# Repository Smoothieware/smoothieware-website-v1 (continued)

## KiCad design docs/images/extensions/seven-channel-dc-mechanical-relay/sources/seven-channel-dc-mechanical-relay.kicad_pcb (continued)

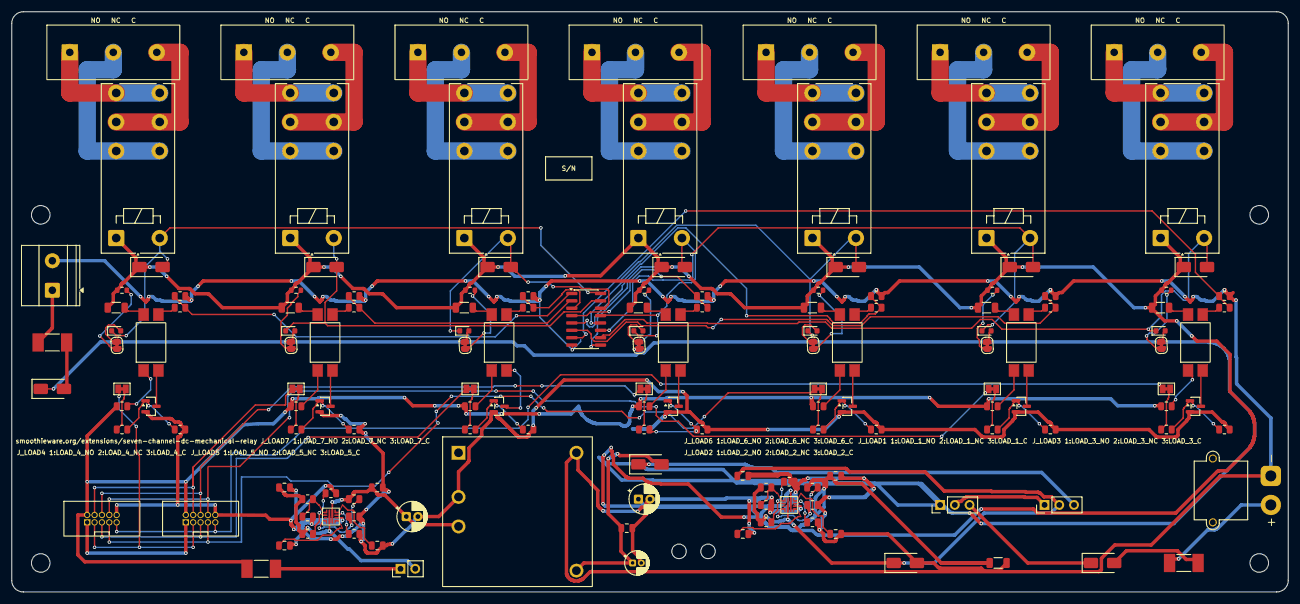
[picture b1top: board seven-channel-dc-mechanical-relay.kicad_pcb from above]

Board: 2 copper layers, 220.0 x 100.0 mm, 157 parts (1 on the bottom side), 128 nets.

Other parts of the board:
CT1, CT2: CABLE TIE; CableTie_NPTH_2_5mm
H1, H2, H3, H4: MountingHole_3.2mm_M3

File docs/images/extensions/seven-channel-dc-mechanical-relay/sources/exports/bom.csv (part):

Reference,Value,Footprint,DNP,Excluded_from_BOM,Manufacturer_part_number,Procurement_status,Assembly_role
CT1,CABLE TIE,Fancification_Mechanical:CableTie_NPTH_2_5mm,False,True,,Retained baseline item; exact procurement mapping/availability requires review,Mechanical/no purchase line
CT2,CABLE TIE,Fancification_Mechanical:CableTie_NPTH_2_5mm,False,True,,Retained baseline item; exact procurement mapping/availability requires review,Mechanical/no purchase line
C_ARRAY1,885012207098,Capacitor_SMD:C_0805_2012Metric,False,False,885012207098,Exact ordering choice; supplier stock/format/MOQ not qualified,SMT; assembler eligibility/orientation requires approval
C_COIL_BULK1,47uF 25V,Capacitor_THT:CP_Radial_D5.0mm_P2.00mm,False,False,EEUFR1E470,Exact ordering choice; supplier stock/format/MOQ not qualified,Through-hole hand-fit; exclude from SMT placement import
C_COIL_DVDT1,10nF 50V,Capacitor_SMD:C_0805_2012Metric,False,False,,Retained baseline item; exact procurement mapping/availability requires review,SMT; assembler eligibility/orientation requires approval
C_COIL_IN1,100nF 35V,Capacitor_SMD:C_0805_2012Metric,False,False,,Retained baseline item; exact procurement mapping/availability requires review,SMT; assembler eligibility/orientation requires approval
C_COIL_ITIMER1,2.2nF 16V,Capacitor_SMD:C_0805_2012Metric,False,False,,Retained baseline item; exact procurement mapping/availability requires review,SMT; assembler eligibility/orientation requires approval
C_COIL_OUT1,100nF 35V,Capacitor_SMD:C_0805_2012Metric,False,False,,Retained baseline item; exact procurement mapping/availability requires review,SMT; assembler eligibility/orientation requires approval
C_HOST_DVDT1,10nF 50V,Capacitor_SMD:C_0805_2012Metric,False,False,,Retained baseline item; exact procurement mapping/availability requires review,SMT; assembler eligibility/orientation requires approval
C_HOST_IN1,100nF 25V,Capacitor_SMD:C_0805_2012Metric,False,False,,Retained baseline item; exact procurement mapping/availability requires review,SMT; assembler eligibility/orientation requires approval
C_HOST_ITIMER1,2.2nF 16V,Capacitor_SMD:C_0805_2012Metric,False,False,,Retained baseline item; exact procurement mapping/availability requires review,SMT; assembler eligibility/orientation requires approval
C_HOST_OUT1,100nF 25V,Capacitor_SMD:C_0805_2012Metric,False,False,,Retained baseline item; exact procurement mapping/availability requires review,SMT; assembler eligibility/orientation requires approval
C_ISO_BYP1,100nF 25V,Capacitor_SMD:C_0805_2012Metric,False,False,,Retained baseline item; exact procurement mapping/availability requires review,SMT; assembler eligibility/orientation requires approval
C_ISO_IN1,100uF 16V,Capacitor_THT:CP_Radial_D5.0mm_P2.00mm,False,False,,Retained baseline item; exact procurement mapping/availability requires review,Through-hole hand-fit; exclude from SMT placement import
C_ISO_PRE1,10uF 25V,Capacitor_THT:CP_Radial_D4.0mm_P1.50mm,False,False,,Retained baseline item; exact procurement mapping/availability requires review,Through-hole hand-fit; exclude from SMT placement import
D_FLY1,SS16-E3/61T,Diode_SMD:D_SMA,False,False,,Retained baseline item; exact procurement mapping/availability requires review,SMT; assembler eligibility/orientation requires approval
D_FLY2,SS16-E3/61T,Diode_SMD:D_SMA,False,False,,Retained baseline item; exact procurement mapping/availability requires review,SMT; assembler eligibility/orientation requires approval
D_FLY3,SS16-E3/61T,Diode_SMD:D_SMA,False,False,,Retained baseline item; exact procurement mapping/availability requires review,SMT; assembler eligibility/orientation requires approval
D_FLY4,SS16-E3/61T,Diode_SMD:D_SMA,False,False,,Retained baseline item; exact procurement mapping/availability requires review,SMT; assembler eligibility/orientation requires approval
D_FLY5,SS16-E3/61T,Diode_SMD:D_SMA,False,False,,Retained baseline item; exact procurement mapping/availability requires review,SMT; assembler eligibility/orientation requires approval
D_FLY6,SS16-E3/61T,Diode_SMD:D_SMA,False,False,,Retained baseline item; exact procurement mapping/availability requires review,SMT; assembler eligibility/orientation requires approval
D_FLY7,SS16-E3/61T,Diode_SMD:D_SMA,False,False,,Retained baseline item; exact procurement mapping/availability requires review,SMT; assembler eligibility/orientation requires approval
D_IND1,GREEN,LED_SMD:LED_0603_1608Metric,False,False,,Retained baseline item; exact procurement mapping/availability requires review,SMT; assembler eligibility/orientation requires approval
D_IND2,GREEN,LED_SMD:LED_0603_1608Metric,False,False,,Retained baseline item; exact procurement mapping/availability requires review,SMT; assembler eligibility/orientation requires approval
D_IND3,GREEN,LED_SMD:LED_0603_1608Metric,False,False,,Retained baseline item; exact procurement mapping/availability requires review,SMT; assembler eligibility/orientation requires approval
D_IND4,GREEN,LED_SMD:LED_0603_1608Metric,False,False,,Retained baseline item; exact procurement mapping/availability requires review,SMT; assembler eligibility/orientation requires approval
D_IND5,GREEN,LED_SMD:LED_0603_1608Metric,False,False,,Retained baseline item; exact procurement mapping/availability requires review,SMT; assembler eligibility/orientation requires approval
D_IND6,GREEN,LED_SMD:LED_0603_1608Metric,False,False,,Retained baseline item; exact procurement mapping/availability requires review,SMT; assembler eligibility/orientation requires approval
D_IND7,GREEN,LED_SMD:LED_0603_1608Metric,False,False,,Retained baseline item; exact procurement mapping/availability requires review,SMT; assembler eligibility/orientation requires approval
D_ISO_BLOCK1,B360A,Diode_SMD:D_SMA,False,False,,Retained baseline item; exact procurement mapping/availability requires review,SMT; assembler eligibility/orientation requires approval
D_TERM1,B360A,Diode_SMD:D_SMA,False,False,,Retained baseline item; exact procurement mapping/availability requires review,SMT; assembler eligibility/orientation requires approval
D_TVS1,SMAJ15A,Diode_SMD:D_SMA,False,False,,Retained baseline item; exact procurement mapping/availability requires review,SMT; assembler eligibility/orientation requires approval
D_XT30,B360A,Diode_SMD:D_SMA,False,False,,Retained baseline item; exact procurement mapping/availability requires review,SMT; assembler eligibility/orientation requires approval
F_HOST1,0452003.MRL,Fuse:Fuse_Littelfuse-NANO2-451_453,False,False,,Retained baseline item; exact procurement mapping/availability requires review,SMT; assembler eligibility/orientation requires approval
F_TERM1,045201.5MRL,Fuse:Fuse_Littelfuse-NANO2-451_453,False,False,,Retained baseline item; exact procurement mapping/availability requires review,SMT; assembler eligibility/orientation requires approval
F_XT30,045201.5MRL,Fuse:Fuse_Littelfuse-NANO2-451_453,False,False,,Retained baseline item; exact procurement mapping/availability requires review,SMT; assembler eligibility/orientation requires approval
H1,MountingHole_3.2mm_M3,MountingHole_3.2mm_M3,False,True,,Retained baseline item; exact procurement mapping/availability requires review,Mechanical/no purchase line
H2,MountingHole_3.2mm_M3,MountingHole_3.2mm_M3,False,True,,Retained baseline item; exact procurement mapping/availability requires review,Mechanical/no purchase line
H3,MountingHole_3.2mm_M3,MountingHole_3.2mm_M3,False,True,,Retained baseline item; exact procurement mapping/availability requires review,Mechanical/no purchase line
H4,MountingHole_3.2mm_M3,MountingHole_3.2mm_M3,False,True,,Retained baseline item; exact procurement mapping/availability requires review,Mechanical/no purchase line
JP1,CUT TO DISABLE D_IND3,Jumper:SolderJumper-2_P1.3mm_Bridged_RoundedPad1.0x1.5mm,False,True,,Retained baseline item; exact procurement mapping/availability requires review,Copper jumper; no purchased part
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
